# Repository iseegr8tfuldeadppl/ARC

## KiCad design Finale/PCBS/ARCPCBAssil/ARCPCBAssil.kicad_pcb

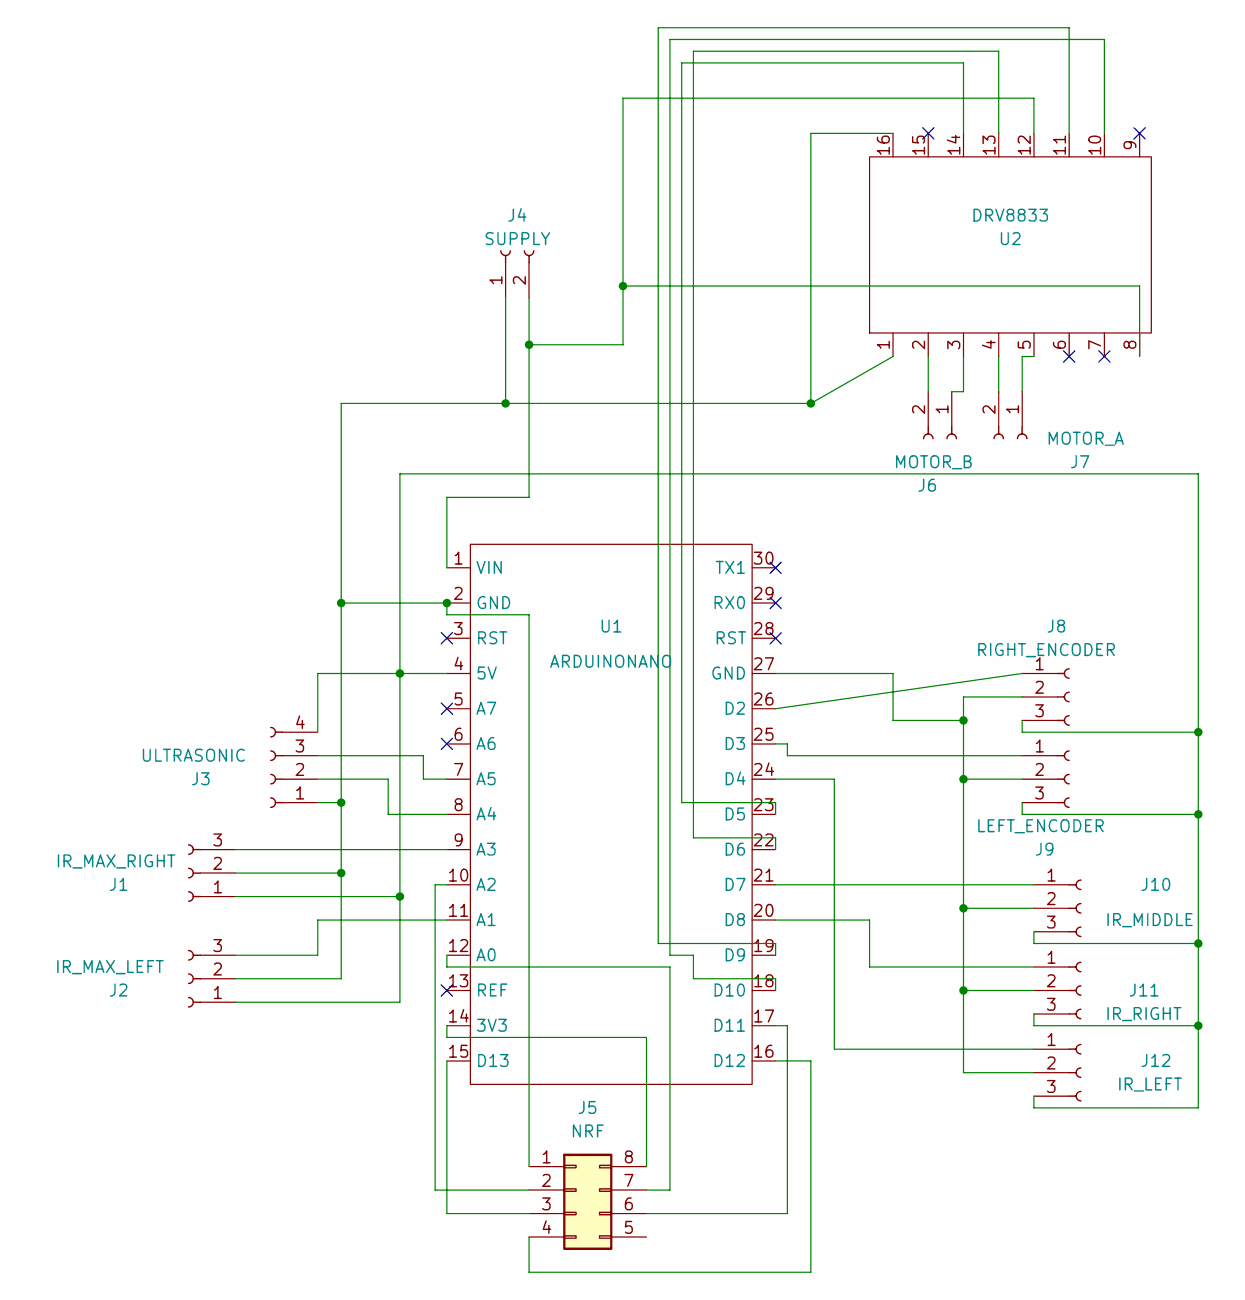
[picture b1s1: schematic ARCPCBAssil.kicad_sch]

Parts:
J1: IR_MAX_RIGHT; PinSocket_1x03_P2.54mm_Vertical
J2: IR_MAX_LEFT; PinSocket_1x03_P2.54mm_Vertical
J3: ULTRASONIC; PinSocket_1x04_P2.54mm_Vertical
J4: SUPPLY; TerminalBlock_Phoenix_MPT-0,5-2-2.54_1x02_P2.54mm_Horizontal
J5: NRF; PinSocket_2x04_P2.54mm_Vertical
J6: MOTOR_B; TerminalBlock_Phoenix_MPT-0,5-2-2.54_1x02_P2.54mm_Horizontal
J7: MOTOR_A; TerminalBlock_Phoenix_MPT-0,5-2-2.54_1x02_P2.54mm_Horizontal
J8: RIGHT_ENCODER; PinSocket_1x03_P2.54mm_Vertical
J9: LEFT_ENCODER; PinSocket_1x03_P2.54mm_Vertical
J10: IR_MIDDLE; PinSocket_1x03_P2.54mm_Vertical
J11: IR_RIGHT; PinSocket_1x03_P2.54mm_Vertical
J12: IR_LEFT; PinSocket_1x03_P2.54mm_Vertical
U1: ARDUINONANO
U2: DRV8833

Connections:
unnamed: J1.1, J2.1, J3.4, J8.3, J9.3, J10.3, J11.3, J12.3, U1.4 (5V)
unnamed: J1.2, J2.2, J3.1, J4.1, J5.1, U1.2 (GND), U2.1, U2.16
unnamed: J1.3, U1.9 (A3)
unnamed: J2.3, U1.11 (A1)
unnamed: J3.2, U1.8 (A4)
unnamed: J3.3, U1.7 (A5)
unnamed: J4.2, U1.1 (VIN), U2.8, U2.12
unnamed: J5.2, U1.10 (A2)
unnamed: J5.3, U1.15 (D13)
unnamed: J5.4, U1.16 (D12)
unnamed: J5.6, U1.17 (D11)
unnamed: J5.7, U1.12 (A0)
unnamed: J5.8, U1.14 (3V3)
unnamed: J6.1, U2.3
unnamed: J6.2, U2.2
unnamed: J7.1, U2.5
unnamed: J7.2, U2.4
unnamed: J8.1, U1.26 (D2)
unnamed: J9.1, U1.25 (D3)
unnamed: J10.1, U1.21 (D7)
unnamed: J8.2, J9.2, J10.2, J11.2, J12.2, U1.27 (GND)
unnamed: J11.1, U1.20 (D8)
unnamed: J12.1, U1.24 (D4)
unnamed: U1.18 (D10), U2.10
unnamed: U1.19 (D9), U2.11
unnamed: U1.22 (D6), U2.13
unnamed: U1.23 (D5), U2.14

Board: 2 copper layers, 14 parts (0 on the bottom side), 27 nets, no tracks yet.

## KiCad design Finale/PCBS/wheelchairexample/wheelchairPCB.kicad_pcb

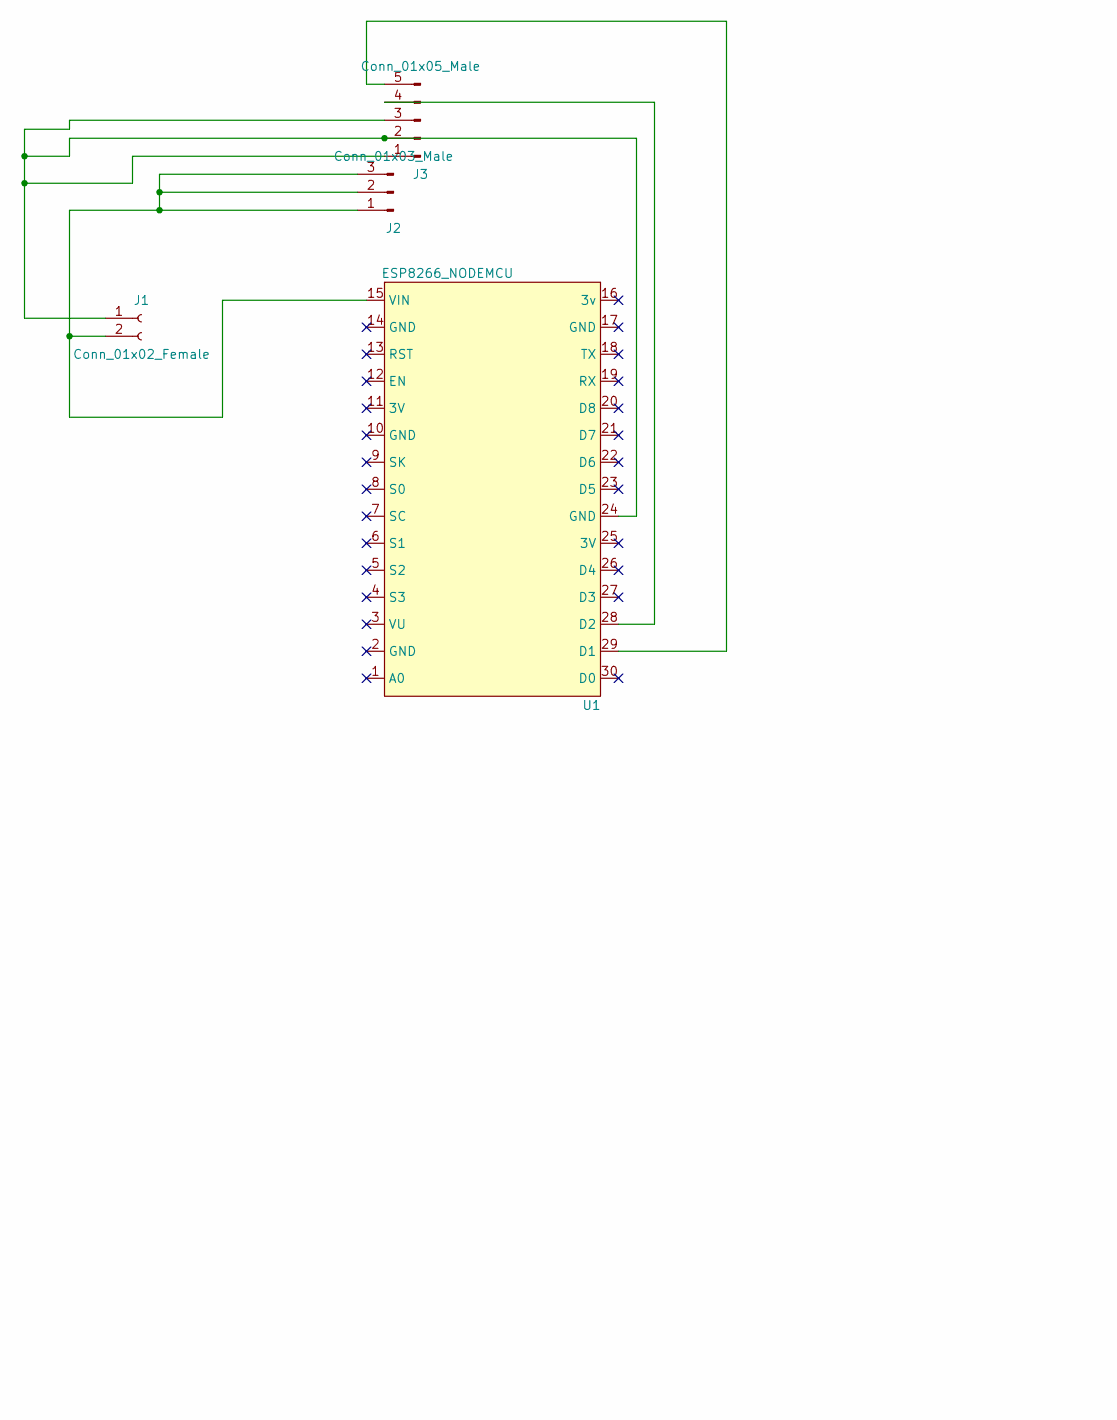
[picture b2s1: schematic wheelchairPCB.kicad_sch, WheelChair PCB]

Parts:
J1: Conn_01x02_Female; PinSocket_1x02_P2.54mm_Vertical
J2: Conn_01x03_Male; PinHeader_1x03_P2.54mm_Vertical
J3: Conn_01x05_Male; PinHeader_1x05_P2.54mm_Vertical
U1: ESP8266_NODEMCU; ESP8266NODEMCU

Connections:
unnamed: J1.1, J3.1, J3.2, J3.3, U1.24 (GND)
unnamed: J1.2, J2.1, J2.2, J2.3, U1.15 (VIN)
unnamed: J3.4, U1.28 (D2)
unnamed: J3.5, U1.29 (D1)

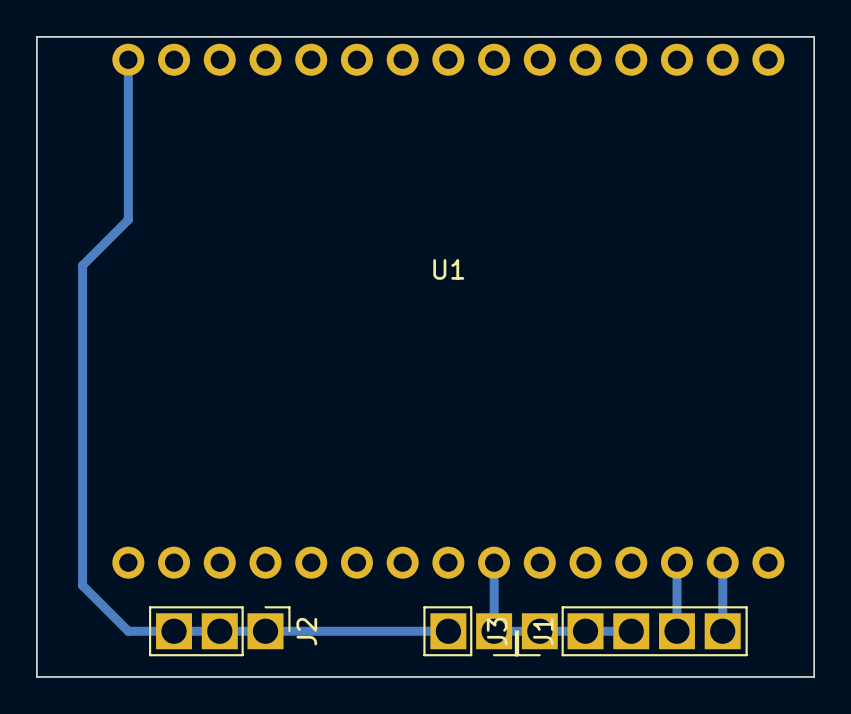
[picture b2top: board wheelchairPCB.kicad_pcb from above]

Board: 2 copper layers, 43.2 x 35.6 mm, 4 parts (0 on the bottom side), 4 nets.

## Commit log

2022-03-26 organized
2022-08-20 Arm (custom position courses for each shape)
2022-08-21 Arm is picking up the cube now
2022-08-22 3D Models (modeled a new large carriage
2022-08-22 NRF (made it work, sending a msg and waiting for reply
2022-08-22 NRF (cleaned code up)
2022-08-22 Cargo (added Ui and moving sequence for cargo mode)
2022-08-24 Arm (modeled a new gripper)
2022-08-24 Redo
2022-08-24 Arm (modified previous app i made to control arm manually)
2022-08-24 Arm (almost finished with manual arm app, more automation integrated)
2022-08-24 Arm&Vision (detection and pickup are doing successful)
2022-08-24 Cargo Pass (made manual control from app work), added some more optimization
2022-08-24 Bug fixes (removed performance worsening feature)
2022-08-26 Radio Communication good, New cargo, cargo pinners, bug fixes
2022-08-26 Reorganization, finetuning rehearsals process
2022-08-27 PCB, and 3D modeled a bottom base padding for robot arm to prevent getting stuck around edges
2022-08-27 Going to switch back to canny
2022-08-28 Working out canny
2022-08-28 MorphologyEx is promising, saving it (check cam_test.py
2022-08-28 Detecting circles using HoughCircles
2022-08-28 Cam testing
2022-08-28 Green cube doing well with my canny
2022-08-28 in bilateral.py i got triangles and cubes to be detected reliably, currently only tested green and yellow, arguably the hardest ones but didn't test with a stripped table like theirs, i might have to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
2022-08-28 First working one, in bilateral.py
2022-08-28 Successfully integrated new bilateral.py edge detection into main.py without completely removing 1st method just incase
2022-08-29 3D modeled breadboard enclosure, diy'ed the carriage holder by reusing a part from the 6 legged or 4 legged spider robot, it fit perfectly between the strips of the cargo and i glued it into the old 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
2022-08-29 3D Model, cargo handle, breadboard box finalized
2022-08-30 Save before rehearsals 8/30/2022
2022-08-30 rehearsals (bug fixes) some duplication and crash bugs that idk the source of it's extremely weird, they get repoirted in a oneliner but no source
2022-08-30 Did more rehearsals
2022-08-31 NRF bug fixes, now mode between nrf and cargo is reported to the app, synced position between 2nd app and robot, no more sudden boom
2022-08-31 designed cargo aid parts, and attempting encoder
2022-08-31 just pinout diagrams for pcbs
2022-08-31 improved vision, cleaned up code, added one more position to robot arm solving shapes being too close or too far problem, bug fixes, added an opencv menu for switching modes, performance improvements
2022-09-01 First realistic rehearsal (pointed out a big problem in car wheels)
2022-09-01 Automatically moving onto line follower mode, cleaned robot up, increased cargo box size for safety, bug fixes, code cleanup
2022-09-01 Tuning and bug testing
2022-09-02 most remaining bugs fixed, more automation and dispurtion strategy in full swing, line follower bug fixes, every value is hardcoded as backup in case of corruption of pickle file, needs some time opt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
2022-09-17 cleanup
2022-09-17 nrf modified
2022-09-21 updated gitignore

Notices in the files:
Finale/PCBS/wheelchairexample/wheelchairPCB.kicad_sch:
Licence: KRIMZON Kream
